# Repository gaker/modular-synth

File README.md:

# Modular Synth

A dumping ground for synthesizer modules, PCBs, etc.

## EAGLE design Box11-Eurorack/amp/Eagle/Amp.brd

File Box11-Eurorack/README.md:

# Box11 Eurorack

I love synthesizers.com modules. I also love eurorack modules This is an attempt to marry the two using a full-width faceplate to house 3U 
modules, as well as add in some other goodies.

I've gone with the [Box11 system](https://shop.synthesizers.com/products/qcb11) for all of my DotCom modules, and want to integrate those into eurorack. I've been rocking with the 64HP moog skiffs, they are full, so it is time to do something else.

The following gives me 104hp of eurorack space in a synthesizers.com Box 11 frame. With about 1.5U or so of space, I decided to go all in and have fun taking up the space.

## Faceplate

Status: in progress.

## Utilities

With ~1.5U of space just sitting there begging to have cables and modules
attached, I would be remiss if I didn't take advantage of all of this 
real estate.   

### 1/4" to 1/8" passive passthrough

* Switchcraft [35rm3s](https://www.switchcraft.com/3-5mm-stereo-jack-rear-mount-locking-sealed-rohs/35rm3s/) 1/8" Jacks
* Switchcraft [112ax](https://www.switchcraft.com/single-closed-circuit-solder-lug-termination/112ax/) 1/4" Jacks

### Fork

Simple 1 -> 3 (x2) buffered mults.

Power in:

    * +12V
    * -12V
    * GND

Via a [TE 640456-3](https://www.mouser.com/ProductDetail/571-6404563) from the Oscillator.

### Voice

VCO built on the [AS3340](https://www.alfarzpp.lv/eng/sc/AS3340.pdf) Oscillator.

### Sway

3x Attack/Release Envelope generators.
Gate one is normalized to gate 2

### Tone

VCF built on the [AS3320](https://www.alfarzpp.lv/eng/sc/AS3320.pdf)

### AMP

VCA built on the [AS3360](https://www.alfarzpp.lv/eng/sc/AS3360.pdf).
Powers two Hairball Audio 8045 VU Meters.

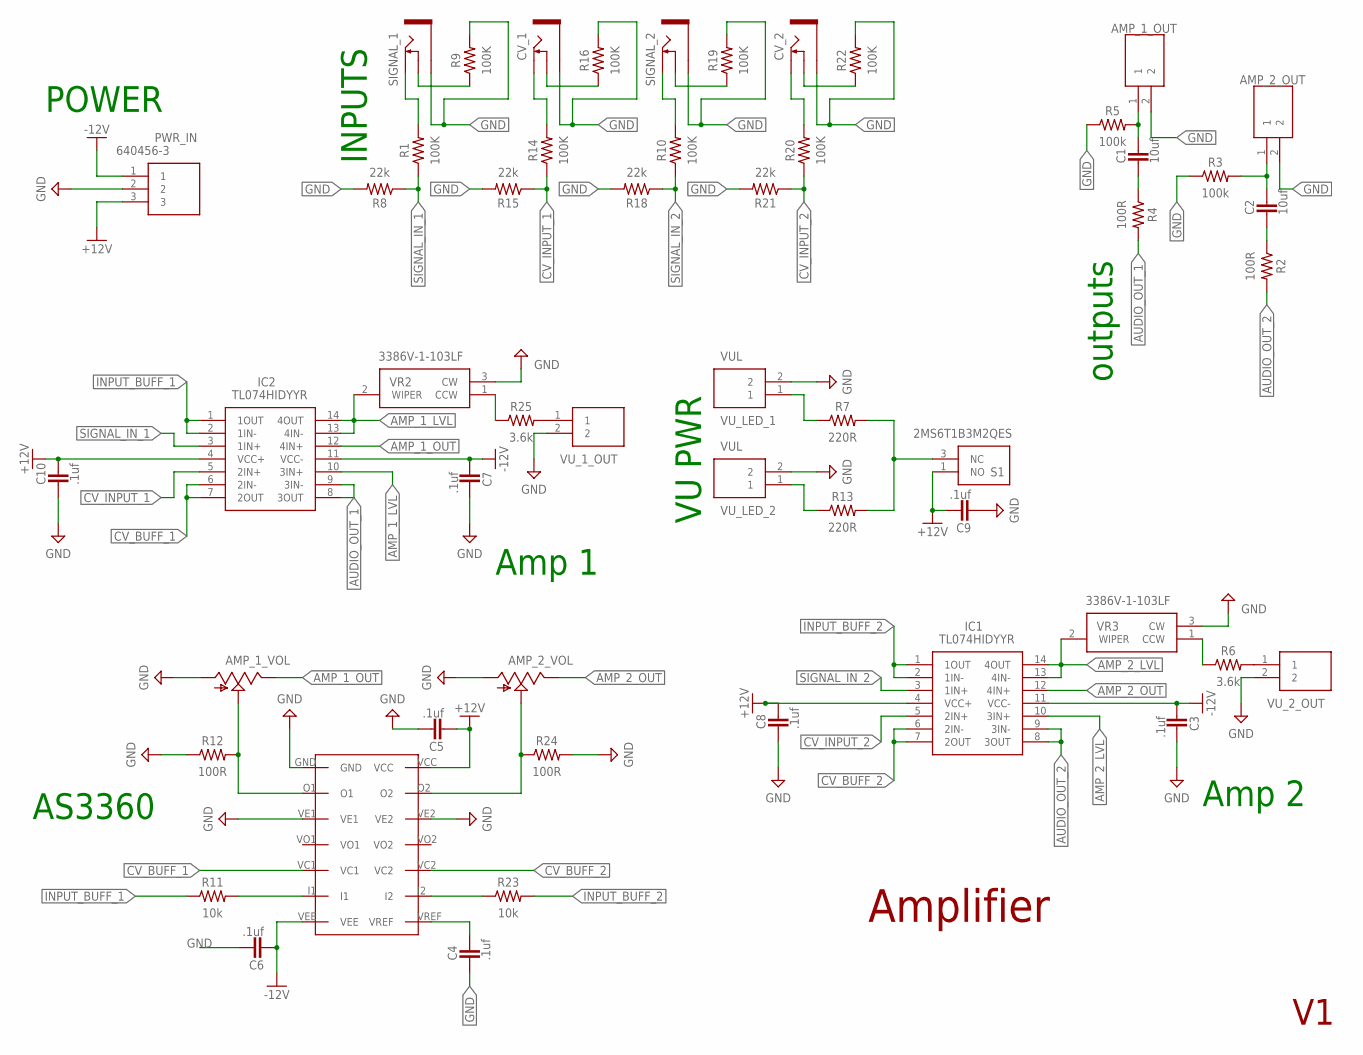
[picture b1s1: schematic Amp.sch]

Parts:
AMP_1_OUT, AMP_2_OUT: OUT; SHDR2W66P0X254_1X2_508X572X104
AMP_1_VOL, AMP_2_VOL: 9MM_SNAP-IN_POT_; 9MM_SNAP-IN_POT
C1, C2: 10uf; CAPM3216X180
C3, C4, C5, C6, C7, C8, C9, C10: .1uf; CAPC1005X60
CV_1, CV_2: THONKICONNNEW; WQP-PJ301M-12_JACK
IC1, IC2: TL074HIDYYR; SOP50P326X110-14N
PWR_IN: 640456-3; HDRV3W107P0X254_1X3_762X572X10
R1, R9, R10, R14, R16, R19, R20, R22: 100K; RESC1005X40
R2, R4, R12, R24: 100R; RESC1005X40
R3, R5: 100k; RESC1005X40
R6, R25: 3.6k; RESC1005X40
R7, R13: 220R; RESC1005X40
R8, R15, R18, R21: 22k; RESC1005X40
R11, R23: 10k; RESC1005X40
S1: 2MS6T1B3M2QES
SIGNAL_1, SIGNAL_2: THONKICONNNEW; WQP-PJ301M-12_JACK
U$1: AS3360
VR2, VR3: 3386V-1-103LF; 3386V1103LF
VU_1_OUT, VU_2_OUT: VUO; SHDR2W66P0X254_1X2_508X572X104
VU_LED_1, VU_LED_2: VUL; SHDR2W66P0X254_1X2_508X572X104

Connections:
+12V: C5.2, C8.1, C9.1, C10.1, IC1.4 (VCC+), IC2.4 (VCC+), PWR_IN.3, S1.1 (NO), U$1.VCC
-12V: C3.2, C6.2, C7.2, IC1.11 (VCC-), IC2.11 (VCC-), PWR_IN.1, U$1.VEE
AMP_1_LVL: IC2.10 (3IN+), IC2.13 (4IN-), IC2.14 (4OUT), VR2.2 (WIPER)
AMP_1_OUT: AMP_1_VOL.2 (S), AMP_1_VOL.3 (E), IC2.12 (4IN+), R12.2, U$1.O1
AMP_2_LVL: IC1.10 (3IN+), IC1.13 (4IN-), IC1.14 (4OUT), VR3.2 (WIPER)
AMP_2_OUT: AMP_2_VOL.2 (S), AMP_2_VOL.3 (E), IC1.12 (4IN+), R24.1, U$1.O2
AUDIO_OUT_1: IC2.8 (3OUT), IC2.9 (3IN-), R4.2
AUDIO_OUT_2: IC1.8 (3OUT), IC1.9 (3IN-), R2.2
CV_BUFF_1: IC2.6 (2IN-), IC2.7 (2OUT), U$1.VC1
CV_BUFF_2: IC1.6 (2IN-), IC1.7 (2OUT), U$1.VC2
CV_INPUT_1: IC2.5 (2IN+), R14.1, R15.1
CV_INPUT_2: IC1.5 (2IN+), R20.1, R21.1
GND: AMP_1_OUT.2, AMP_1_VOL.1 (A), AMP_2_OUT.2, AMP_2_VOL.1 (A), C3.1, C4.2, C5.1, C6.1, C7.1, C8.2, C9.2, C10.2, CV_1.P$3_SLEEVE (SLEEVE), CV_2.P$3_SLEEVE (SLEEVE), PWR_IN.2, R3.1, R5.1, R8.2, R9.2, R12.1, R15.2, R16.2, R18.2, R19.2, R21.2, R22.2, R24.2, SIGNAL_1.P$3_SLEEVE (SLEEVE), SIGNAL_2.P$3_SLEEVE (SLEEVE), U$1.GND, U$1.VE1, U$1.VE2, VR2.3 (CW), VR3.3 (CW), VU_1_OUT.2, VU_2_OUT.2, VU_LED_1.2, VU_LED_2.2
INPUT_BUFF_1: IC2.1 (1OUT), IC2.2 (1IN-), R11.1
INPUT_BUFF_2: IC1.1 (1OUT), IC1.2 (1IN-), R23.2
unnamed: AMP_2_OUT.1, C2.1, R3.2
unnamed: AMP_1_OUT.1, C1.1, R5.2
unnamed: C1.2, R4.1
unnamed: C2.2, R2.1
unnamed: R13.1, VU_LED_2.1
unnamed: R7.1, VU_LED_1.1
unnamed: C4.1, U$1.VREF
unnamed: R6.1, VR3.1 (CCW)
unnamed: R6.2, VU_2_OUT.1
unnamed: R11.2, U$1.I1
unnamed: R10.2, SIGNAL_2.P$1_TIP (TIP)
unnamed: R1.2, SIGNAL_1.P$1_TIP (TIP)
unnamed: R9.1, SIGNAL_1.P$2_SWITCH (SWITCH)
unnamed: CV_1.P$1_TIP (TIP), R14.2
unnamed: CV_1.P$2_SWITCH (SWITCH), R16.1
unnamed: R19.1, SIGNAL_2.P$2_SWITCH (SWITCH)
unnamed: CV_2.P$1_TIP (TIP), R20.2
unnamed: CV_2.P$2_SWITCH (SWITCH), R22.1
unnamed: R23.1, U$1.I2
unnamed: R7.2, R13.2, S1.3 (NC)
unnamed: R25.2, VU_1_OUT.1
unnamed: R25.1, VR2.1 (CCW)
SIGNAL_IN_1: IC2.3 (1IN+), R1.1, R8.1
SIGNAL_IN_2: IC1.3 (1IN+), R10.1, R18.1

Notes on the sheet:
Amplifier
POWER
outputs
AS3360
INPUTS
Amp 1
VU PWR
Amp 2

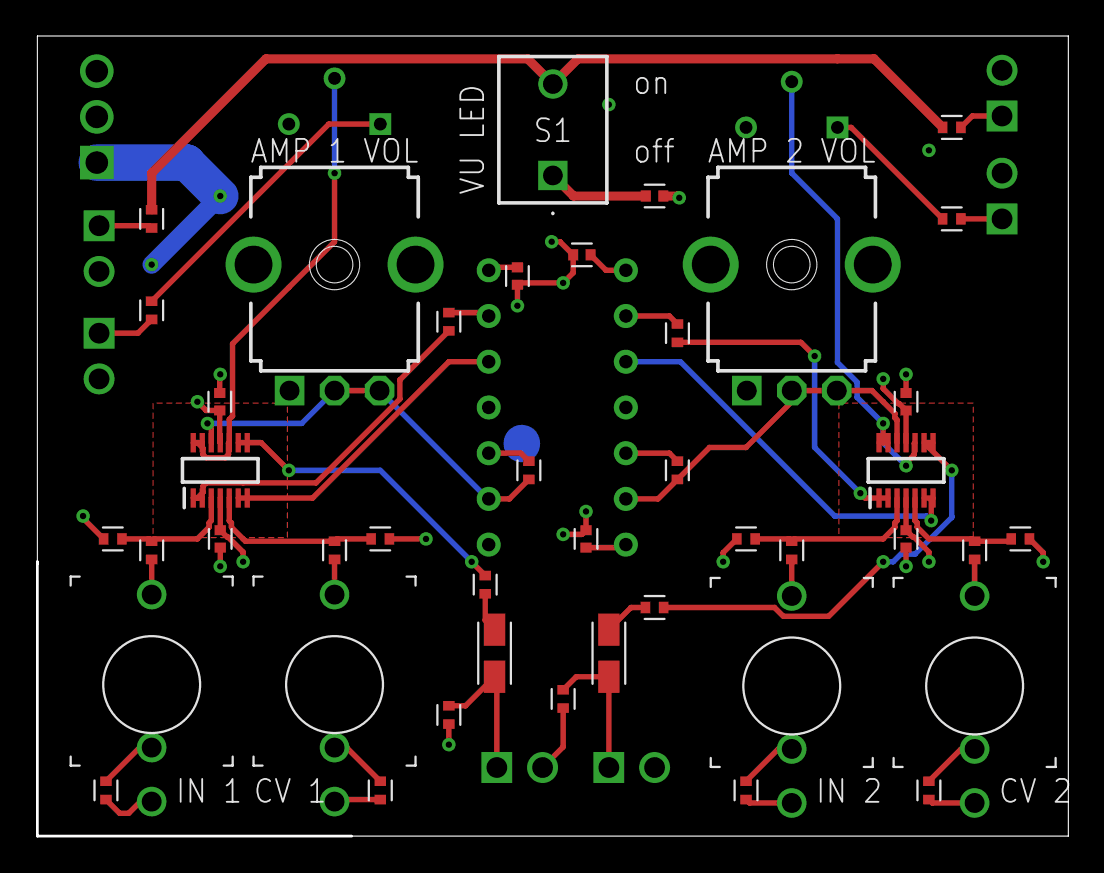
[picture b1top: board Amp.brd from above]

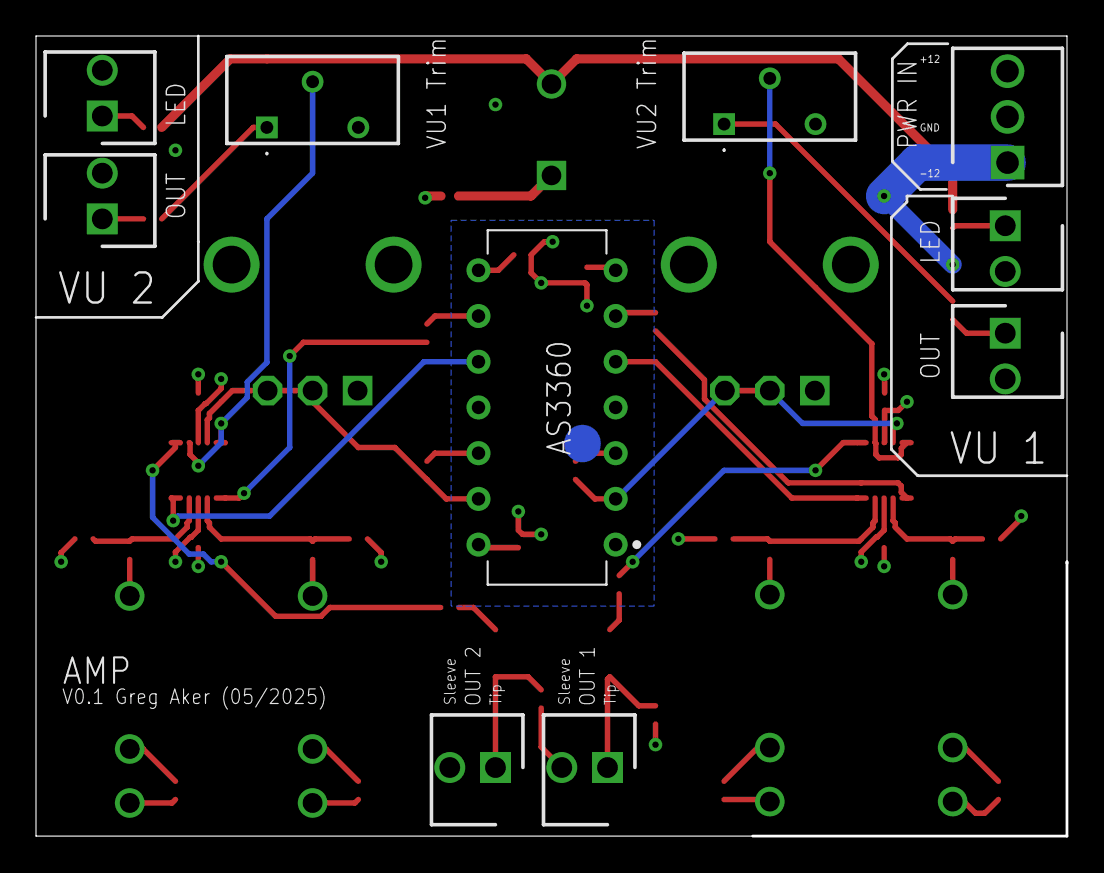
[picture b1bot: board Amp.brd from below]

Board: 4 copper layers, 57.2 x 44.4 mm, 53 parts (10 on the bottom side), 39 nets.

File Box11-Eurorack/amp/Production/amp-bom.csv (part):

Part,Value,Device,Package,Description,CATEGORY,DATASHEET,DESCRIPTION,HEIGHT,MANUFACTURER,MANUFACTURER_NAME,MANUFACTURER_PART_NUMBER,MOUSER_PART_NUMBER,MOUSER_PRICE-STOCK,MPN,OPERATING_TEMP,OPERATING_TEMPERATURE,PACKAGE_SIZE,PACKAGE_TYPE,PART_STATUS,ROHS,ROHS_COMPLIANT,SERIES,SPICEMODEL,SPICEMODELTEXT,SPICEPREFIX,SUB-CATEGORY,SUBCATEGORY,TEMPERATURE_COEFFICIENT,THERMALLOSS,TOLERANCE,TYPE,VOLTAGE_RATING
AMP_1_OUT,OUT,640456-2,SHDR2W66P0X254_1X2_508X572X104,"Body Features: Primary Product Color Natural | Configuration Features: Number of Positions 2 | Number of Columns 2 | PCB Mount Orientation Vertical | Number of Rows 1 | Contact Features: Contact Mating Area Length 7.49 MM | Contact Shape & Form Square | Contact Layout Inline | Contact Mating Area Plating Material Thickness 3.81 MICM | Contact Mating Area Plating Material Thickness 150 MICIN | Contact Underplating Material Thickness 1.27 MICM | Contact Mating Area Length .295 INCH | PCB Contact Termination A",,,"Body Features: Primary Product Color Natural | Configuration Features: Number of Positions 2 | Number of Columns 2 | PCB Mount Orientation Vertical | Number of Rows 1 | Contact Features: Contact Mating Area Length 7.49 MM | Contact Shape & Form Square | Contact Layout Inline | Contact Mating Area Plating Material Thickness 3.81 MICM | Contact Mating Area Plating Material Thickness 150 MICIN | Contact Underplating Material Thickness 1.27 MICM | Contact Mating Area Length .295 INCH | PCB Contact Termination A",10.414mm,,"TE Connectivity",640456-2,571-6404562,https://www.mouser.co.uk/ProductDetail/TE-Connectivity-AMP/6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,,,,,,,,,,OutputJack,"*\n.subckt OutputJack 1 2\nR1 1 1_dummy 1m\nR2 2 2_dummy 1m\n.ends OutputJack",X,,,,,,,
AMP_1_VOL,,9MM_SNAP-IN_POT_,9MM_SNAP-IN_POT,"9mm vertical snap-in pot, Alpha / Panasonic style",,,,,,,,,,,,,,,,,,,POT10K,"*\n.subckt POT10K 1 2 3\nRtop 1 2 5k\nRbot 2 3 5k\n.ends POT10K",X,,,,,,,
AMP_2_OUT,OUT,640456-2,SHDR2W66P0X254_1X2_508X572X104,"Body Features: Primary Product Color Natural | Configuration Features: Number of Positions 2 | Number of Columns 2 | PCB Mount Orientation Vertical | Number of Rows 1 | Contact Features: Contact Mating Area Length 7.49 MM | Contact Shape & Form Square | Contact Layout Inline | Contact Mating Area Plating Material Thickness 3.81 MICM | Contact Mating Area Plating Material Thickness 150 MICIN | Contact Underplating Material Thickness 1.27 MICM | Contact Mating Area Length .295 INCH | PCB Contact Termination A",,,"Body Features: Primary Product Color Natural | Configuration Features: Number of Positions 2 | Number of Columns 2 | PCB Mount Orientation Vertical | Number of Rows 1 | Contact Features: Contact Mating Area Length 7.49 MM | Contact Shape & Form Square | Contact Layout Inline | Contact Mating Area Plating Material Thickness 3.81 MICM | Contact Mating Area Plating Material Thickness 150 MICIN | Contact Underplating Material Thickness 1.27 MICM | Contact Mating Area Length .295 INCH | PCB Contact Termination A",10.414mm,,"TE Connectivity",640456-2,571-6404562,https://www.mouser.co.uk/ProductDetail/TE-Connectivity-AMP/6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,,,,,,,,,,OutputJack,"*\n.subckt OutputJack 1 2\nR1 1 1_dummy 1m\nR2 2 2_dummy 1m\n.ends OutputJack",X,,,,,,,
AMP_2_VOL,,9MM_SNAP-IN_POT_,9MM_SNAP-IN_POT,"9mm vertical snap-in pot, Alpha / Panasonic style",,,,,,,,,,,,,,,,,,,POT10K,"*\n.subckt POT10K 1 2 3\nRtop 1 2 5k\nRbot 2 3 5k\n.ends POT10K",X,,,,,,,
C1,10uf,CAPACITOR_TANTALUM-1206(3216-METRIC),CAPM3216X180,"Capacitor - Generic",Capacitor,,,,,,,,,,,,,,,,,,,,,,,,,,,
C2,10uf,CAPACITOR_TANTALUM-1206(3216-METRIC),CAPM3216X180,"Capacitor - Generic",Capacitor,,,,,,,,,,,,,,,,,,,,,,,,,,,
C3,.1uf,CAPACITOR_CHIP-0402(1005-METRIC),CAPC1005X60,"Capacitor - Generic",Capacitor,,,,,,,,,,,,,,,,,,,,,,,,,,,
C4,.1uf,CAPACITOR_CHIP-0402(1005-METRIC),CAPC1005X60,"Capacitor - Generic",Capacitor,,,,,,,,,,,,,,,,,,,,,,,,,,,
C5,.1uf,CAPACITOR_CHIP-0402(1005-METRIC),CAPC1005X60,"Capacitor - Generic",Capacitor,,,,,,,,,,,,,,,,,,,,,,,,,,,
C6,.1uf,CAPACITOR_CHIP-0402(1005-METRIC),CAPC1005X60,"Capacitor - Generic",Capacitor,,,,,,,,,,,,,,,,,,,,,,,,,,,
C7,.1uf,CAPACITOR_CHIP-0402(1005-METRIC),CAPC1005X60,"Capacitor - Generic",Capacitor,,,,,,,,,,,,,,,,,,,,,,,,,,,
C8,.1uf,CAPACITOR_CHIP-0402(1005-METRIC),CAPC1005X60,"Capacitor - Generic",Capacitor,,,,,,,,,,,,,,,,,,,,,,,,,,,
C9,.1uf,CAPACITOR_CHIP-0402(1005-METRIC),CAPC1005X60,"Capacitor - Generic",Capacitor,,,,,,,,,,,,,,,,,,,,,,,,,,,
C10,.1uf,CAPACITOR_CHIP-0402(1005-METRIC),CAPC1005X60,"Capacitor - Generic",Capacitor,,,,,,,,,,,,,,,,,,,,,,,,,,,
CV_1,THONKICONNNEW,THONKICONNNEW,WQP-PJ301M-12_JACK,"3.5mm socket for Eurorack modular synths",,,,,,,,,,,,,,,,,,,,,,,,,,,,
CV_2,THONKICONNNEW,THONKICONNNEW,WQP-PJ301M-12_JACK,"3.5mm socket for Eurorack modular synths",,,,,,,,,,,,,,,,,,,,,,,,,,,,
IC1,TL074HIDYYR,TL074HIDYYR,SOP50P326X110-14N,"Operational Amplifiers - Op Amps Quad, 40-V, 5-MHz, 4-mV offset voltage, 20-V/us, In to V+ op amp with -40 C to 125 C operation",,,"Operational Amplifiers - Op Amps Quad"," 40-V"," 5-MHz"," 4-mV offset voltage"," 20-V/us"," In to V+ op amp with -40 C to 125 C operation",1.1mm,,"Texas Instruments",TL074HIDYYR,595-TL074HIDYYR,https://www.mouser.co.uk/ProductDetail/Texas-Instruments/TL0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,,,,,,,,,,,,,,
IC2,TL074HIDYYR,TL074HIDYYR,SOP50P326X110-14N,"Operational Amplifiers - Op Amps Quad, 40-V, 5-MHz, 4-mV offset voltage, 20-V/us, In to V+ op amp with -40 C to 125 C operation",,,"Operational Amplifiers - Op Amps Quad"," 40-V"," 5-MHz"," 4-mV offset voltage"," 20-V/us"," In to V+ op amp with -40 C to 125 C operation",1.1mm,,"Texas Instruments",TL074HIDYYR,595-TL074HIDYYR,https://www.mouser.co.uk/ProductDetail/Texas-Instruments/TL0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,,,,,,,,,,,,,,
PWR_IN,640456-3,640456-3,HDRV3W107P0X254_1X3_762X572X10,"Body Features: Primary Product Color Natural | Configuration Features: Number of Positions 3 | PCB Mount Orientation Vertical | Number of Rows 1 | Contact Features: Contact Current Rating (Max) 5 AMP | Contact Mating Area Plating Material Tin | Contact Underplating Material Nickel | PCB Contact Termination Area Plating Material Tin | Contact Mating Area Length 7.49 MM | Contact Underplating Material Thickness 50 MICIN | Contact Layout Inline | Contact Mating Area Length .295 INCH | Contact Base Material Cop",,,"Body Features: Primary Product Color Natural | Configuration Features: Number of Positions 3 | PCB Mount Orientation Vertical | Number of Rows 1 | Contact Features: Contact Current Rating (Max) 5 AMP | Contact Mating Area Plating Material Tin | Contact Underplating Material Nickel | PCB Contact Termination Area Plating Material Tin | Contact Mating Area Length 7.49 MM | Contact Underplating Material Thickness 50 MICIN | Contact Layout Inline | Contact Mating Area Length .295 INCH | Contact Base Material Cop",10.795mm,,"TE Connectivity",640456-3,571-6404563,https://www.mouser.co.uk/ProductDetail/TE-Connectivity-AMP/6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,,,,,,,,,,,,,,,,,,,
R1,100K,R-US_CHIP-0402(1005-METRIC),RESC1005X40,"Resistor Fixed - ANSI",Resistors,,"Chip Resistor 1.05 X 0.54 X 0.40 mm body 0402(1005-METRIC) Package",,,,,,,,,,0402,SMD,,,,,,,,,,,,,,
R2,100R,R-US_CHIP-0402(1005-METRIC),RESC1005X40,"Resistor Fixed - ANSI",Resistors,,"Chip Resistor 1.05 X 0.54 X 0.40 mm body 0402(1005-METRIC) Package",,,,,,,,,,0402,SMD,,,,,,,,,,,,,,
R3,100k,R-US_CHIP-0402(1005-METRIC),RESC1005X40,"Resistor Fixed - ANSI",Resistors,,"Chip Resistor 1.05 X 0.54 X 0.40 mm body 0402(1005-METRIC) Package",,,,,,,,,,0402,SMD,,,,,,,,,,,,,,
R4,100R,R-US_CHIP-0402(1005-METRIC),RESC1005X40,"Resistor Fixed - ANSI",Resistors,,"Chip Resistor 1.05 X 0.54 X 0.40 mm body 0402(1005-METRIC) Package",,,,,,,,,,0402,SMD,,,,,,,,,,,,,,
R5,100k,R-US_CHIP-0402(1005-METRIC),RESC1005X40,"Resistor Fixed - ANSI",Resistors,,"Chip Resistor 1.05 X 0.54 X 0.40 mm body 0402(1005-METRIC) Package",,,,,,,,,,0402,SMD,,,,,,,,,,,,,,
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
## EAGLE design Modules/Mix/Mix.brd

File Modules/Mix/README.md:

# Mixer

Here's a very simple mixer 

| Part | Quantity |
|----------|----------|
| [Thonkiconn](https://www.thonk.co.uk/shop/thonkiconn/) | 6 |
| [100k Log Potentiometer](https://www.taydaelectronics.com/100k-ohm-logarithmic-taper-potentiometer-round-shaft-pcb-9mm.html) | 3 |

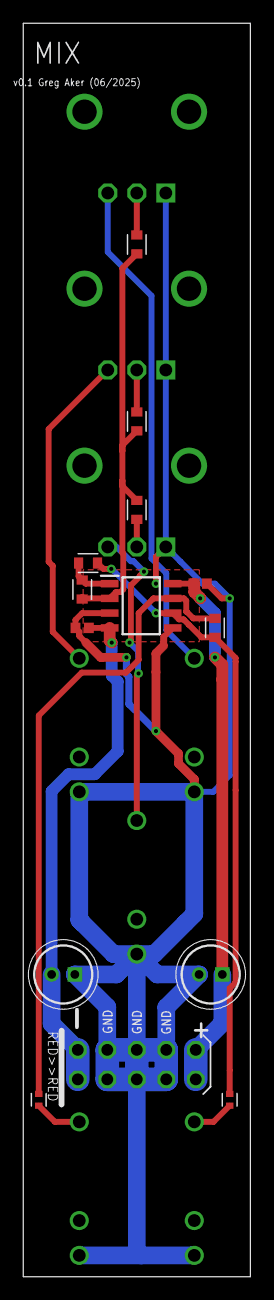
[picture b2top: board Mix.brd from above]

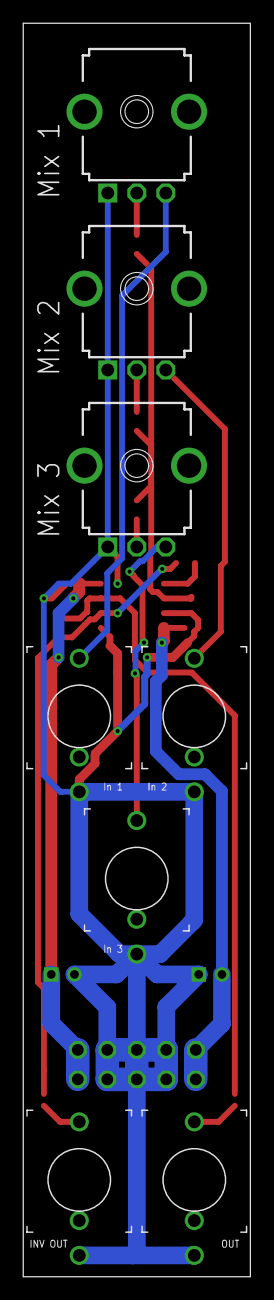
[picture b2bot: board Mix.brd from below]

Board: 2 copper layers, 19.6 x 108.0 mm, 22 parts (8 on the bottom side), 15 nets.

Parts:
C1, C2: 10uf; CAPPRD200W55D500H1200
C3, C4: 0.1uF; 0402
IC1: TL072BIDT; SOIC127P600X175-8N
INV_OUT: THONKICONNNEW; WQP-PJ301M-12_JACK
IN_1, IN_2, IN_3: THONKICONNNEW; WQP-PJ301M-12_JACK
OUT: THONKICONNNEW; WQP-PJ301M-12_JACK
R1, R2, R3, R4, R5, R6: 120k; RESC1608X60
R7, R8: 1k; RESC1005X40
SV1: EURO_POWER_HEADERREGULAR; EURO_POWER_HEADER
VR1, VR2, VR3: 50k; 9MM_SNAP-IN_POT

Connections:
+12V: C2.1, C4.1, IC1.8, SV1.9, SV1.10
-12V: C1.2, C3.1, IC1.4, SV1.1, SV1.2
GND: C1.1, C2.2, C3.2, C4.2, IC1.3, IC1.5, INV_OUT.P$3_SLEEVE, IN_1.P$3_SLEEVE, IN_2.P$3_SLEEVE, IN_3.P$3_SLEEVE, OUT.P$3_SLEEVE, SV1.3, SV1.4, SV1.5, SV1.6, SV1.7, SV1.8, VR1.1, VR2.1, VR3.1
unnamed: IN_1.P$1_TIP, VR1.3
unnamed: IN_2.P$1_TIP, VR2.3
unnamed: IN_3.P$1_TIP, VR3.3
unnamed: R1.1, VR1.2
unnamed: R2.1, VR2.2
unnamed: R3.1, VR3.2
unnamed: IC1.1, R4.2, R5.1
unnamed: IC1.6, R5.2, R6.1, R7.1
unnamed: IC1.2, R1.2, R2.2, R3.2, R4.1
unnamed: IC1.7, R6.2, R8.1
unnamed: INV_OUT.P$1_TIP, R7.2
unnamed: OUT.P$1_TIP, R8.2

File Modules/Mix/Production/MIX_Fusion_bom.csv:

Part,Value,Device,Package,Description,CATEGORY,DATASHEET,DESCRIPTION,HEIGHT,MANUFACTURER,MANUFACTURER_NAME,MANUFACTURER_PART_NUMBER,MOUSER_PART_NUMBER,MOUSER_PRICE-STOCK,MPN,OPERATING_TEMPERATURE,PACKAGE_SIZE,PACKAGE_TYPE,PART_STATUS,PROD_ID,ROHS,SERIES,SUBCATEGORY,TEMPERATURE_COEFFICIENT,THERMALLOSS,TOLERANCE,TYPE,VALUE
C1,10uf,ECE-A1EN100U,CAPPRD200W55D500H1200,"Panasonic 10uF 25 V Aluminium Electrolytic Capacitor, SU Series 1000h 5 x 11mm",,,"Panasonic 10uF 25 V Aluminium Electrolytic Capacitor"," SU Series 1000h 5 x 11mm",12mm,,Panasonic,ECE-A1EN100U,667-ECE-A1EN100U,https://www.mouser.co.uk/ProductDetail/Panasonic/ECE-A1EN100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,,,,,,,,,,,,,
C2,10uf,ECE-A1EN100U,CAPPRD200W55D500H1200,"Panasonic 10uF 25 V Aluminium Electrolytic Capacitor, SU Series 1000h 5 x 11mm",,,"Panasonic 10uF 25 V Aluminium Electrolytic Capacitor"," SU Series 1000h 5 x 11mm",12mm,,Panasonic,ECE-A1EN100U,667-ECE-A1EN100U,https://www.mouser.co.uk/ProductDetail/Panasonic/ECE-A1EN100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,,,,,,,,,,,,,
C3,0.1uF,0.1UF-0402-16V-10%,0402,"0.1µF ceramic capacitors",,,,,,,,,,,,,,,CAP-12416,,,,,,,,0.1uF
C4,0.1uF,0.1UF-0402-16V-10%,0402,"0.1µF ceramic capacitors",,,,,,,,,,,,,,,CAP-12416,,,,,,,,0.1uF
IC1,TL072BIDT,TL072BIDT,SOIC127P600X175-8N,"STMICROELECTRONICS - TL072BIDT - Operational Amplifier, 2 Amplifier, 4 MHz, 16 V/s, 6V to 36V, SOIC, 8 Pins",,,"STMICROELECTRONICS - TL072BIDT - Operational Amplifier"," 2 Amplifier"," 4 MHz"," 16 V/s"," 6V to 36V"," SOIC"," 8 Pins",1.75mm,,STMicroelectronics,TL072BIDT,511-TL072BIDT,https://www.mouser.co.uk/ProductDetail/STMicroelectronics/TL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,,,,,,,,
INV_OUT,THONKICONNNEW,THONKICONNNEW,WQP-PJ301M-12_JACK,"3.5mm socket for Eurorack modular synths",,,,,,,,,,,,,,,,,,,,,,,
IN_1,THONKICONNNEW,THONKICONNNEW,WQP-PJ301M-12_JACK,"3.5mm socket for Eurorack modular synths",,,,,,,,,,,,,,,,,,,,,,,
IN_2,THONKICONNNEW,THONKICONNNEW,WQP-PJ301M-12_JACK,"3.5mm socket for Eurorack modular synths",,,,,,,,,,,,,,,,,,,,,,,
IN_3,THONKICONNNEW,THONKICONNNEW,WQP-PJ301M-12_JACK,"3.5mm socket for Eurorack modular synths",,,,,,,,,,,,,,,,,,,,,,,
OUT,THONKICONNNEW,THONKICONNNEW,WQP-PJ301M-12_JACK,"3.5mm socket for Eurorack modular synths",,,,,,,,,,,,,,,,,,,,,,,
R1,120k,R_CHIP-0603(1608-METRIC),RESC1608X60,"Resistor Fixed - Generic",Resistors,,"Chip Resistor 1.60 X 0.82 X 0.60 mm body 0603(1608-METRIC) Package",,,,,,,,,0603,SMD,,,,,,,,,,
R2,120k,R_CHIP-0603(1608-METRIC),RESC1608X60,"Resistor Fixed - Generic",Resistors,,"Chip Resistor 1.60 X 0.82 X 0.60 mm body 0603(1608-METRIC) Package",,,,,,,,,0603,SMD,,,,,,,,,,
R3,120k,R_CHIP-0603(1608-METRIC),RESC1608X60,"Resistor Fixed - Generic",Resistors,,"Chip Resistor 1.60 X 0.82 X 0.60 mm body 0603(1608-METRIC) Package",,,,,,,,,0603,SMD,,,,,,,,,,
R4,120k,R_CHIP-0603(1608-METRIC),RESC1608X60,"Resistor Fixed - Generic",Resistors,,"Chip Resistor 1.60 X 0.82 X 0.60 mm body 0603(1608-METRIC) Package",,,,,,,,,0603,SMD,,,,,,,,,,
R5,120k,R_CHIP-0603(1608-METRIC),RESC1608X60,"Resistor Fixed - Generic",Resistors,,"Chip Resistor 1.60 X 0.82 X 0.60 mm body 0603(1608-METRIC) Package",,,,,,,,,0603,SMD,,,,,,,,,,
R6,120k,R_CHIP-0603(1608-METRIC),RESC1608X60,"Resistor Fixed - Generic",Resistors,,"Chip Resistor 1.60 X 0.82 X 0.60 mm body 0603(1608-METRIC) Package",,,,,,,,,0603,SMD,,,,,,,,,,
R7,1k,R_CHIP-0402(1005-METRIC),RESC1005X40,"Resistor Fixed - Generic",Resistors,,"Chip Resistor 1.05 X 0.54 X 0.40 mm body 0402(1005-METRIC) Package",,,,,,,,,0402,SMD,,,,,,,,,,
R8,1k,R_CHIP-0402(1005-METRIC),RESC1005X40,"Resistor Fixed - Generic",Resistors,,"Chip Resistor 1.05 X 0.54 X 0.40 mm body 0402(1005-METRIC) Package",,,,,,,,,0402,SMD,,,,,,,,,,
SV1,EURO_POWER_HEADERREGULAR,EURO_POWER_HEADERREGULAR,EURO_POWER_HEADER,"Power Header",,,,,,,,,,,,,,,,,,,,,,,
VR1,50k,9MM_SNAP-IN_POT_,9MM_SNAP-IN_POT,"9mm vertical snap-in pot, Alpha / Panasonic style",,,,,,,,,,,,,,,,,,,,,,,
VR2,50k,9MM_SNAP-IN_POT_,9MM_SNAP-IN_POT,"9mm vertical snap-in pot, Alpha / Panasonic style",,,,,,,,,,,,,,,,,,,,,,,
VR3,50k,9MM_SNAP-IN_POT_,9MM_SNAP-IN_POT,"9mm vertical snap-in pot, Alpha / Panasonic style",,,,,,,,,,,,,,,,,,,,,,,

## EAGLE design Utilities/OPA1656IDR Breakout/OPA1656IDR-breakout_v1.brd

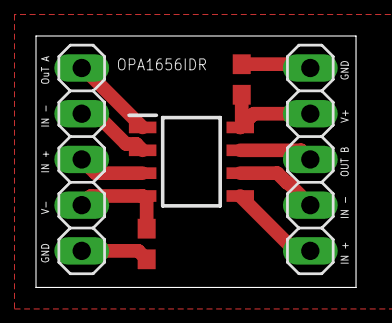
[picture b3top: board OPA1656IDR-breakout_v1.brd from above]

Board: 2 copper layers, 17.8 x 14.0 mm, 5 parts (0 on the bottom side), 9 nets.

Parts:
C1, C2: 0.1uF; 0603
IC1: OPA1656IDR; SOIC127P600X175-8N
JP1, JP2: PINHD-1X5; 1X05

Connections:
GND: C1.1, C2.2, JP1.5, JP2.1
unnamed: IC1.1, JP1.1
unnamed: IC1.2, JP1.2
unnamed: IC1.3, JP1.3
unnamed: C2.1, IC1.4, JP1.4
unnamed: IC1.5, JP2.5
unnamed: IC1.6, JP2.4
unnamed: IC1.7, JP2.3
unnamed: C1.2, IC1.8, JP2.2

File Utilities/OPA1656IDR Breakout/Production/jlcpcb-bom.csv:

Comment,Designator,Footprint,JLCPCB Part #（optional）
0.1uF,C1,0603,C14663
0.1uF,C2,0603,C14663
OPA1656IDR,IC1,SOIC127P600X175-8N,C1849431
,,,
,,,
,,,
,,,

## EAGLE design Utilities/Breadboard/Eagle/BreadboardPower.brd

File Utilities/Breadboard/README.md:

# Breadboard

Simple breadboard adapter for a Meanwell RT65B.

* Provides power filtering to save space on the breadboard.
* +12V/GND / -12V/GND rails to fit on either side of the breadboard.
* Pin header for +3.3v & 5V

Uses a ``TE-Connectivity-AMP/640456-6`` connector to supply power to the board.  Sorry in advance. I have a crimper that can make these cables. If anyone wants a board with something different, I can make one if you wish.

| Pin | Usage |
|-----|-------|
| 1   | +5V   |
| 2   | GND   |
| 3   | NC    |
| 4   | +12V  |
| 5   | NC    |
| 6   | -12V  |

## Cost

Manufactured at [JLCPCB](https://www.jlcpcb.com) in July of 2025 with PCBA assembly (see Production directory for more info).

*PCBA for 5 boards*

| Item                    | Cost       |
|-------------------------|------------|
| Merchandise Total       | $15.75     |
| Shipping Charge         | $37.39     |
| Customs duties & taxes  | $8.67      |
| Sales Tax               | $4.25      |
| **Order Total**         | **$66.06** | 

## Safety with the power supply

Your mileage may vary, and do this at your own risk, k?  This power supply is a bit scary for desk usage since the line-level voltages can easily be touched. That could mean a very bad day for you and your loved ones.  I wired up a line cord and then used hot glue to cover the terminals taking extra care to test continuity everywhere to ensure this doesn't shock me by being on my benchtop.  I also keep it in a little box I drilled holes into. 

But you do you. Whatever you think makes sense.

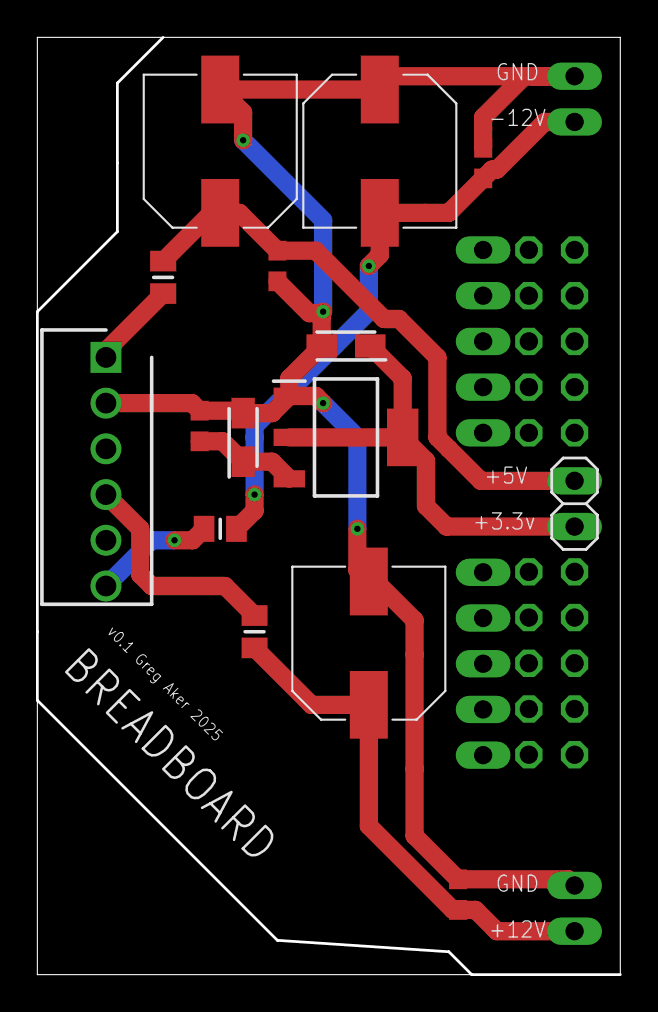
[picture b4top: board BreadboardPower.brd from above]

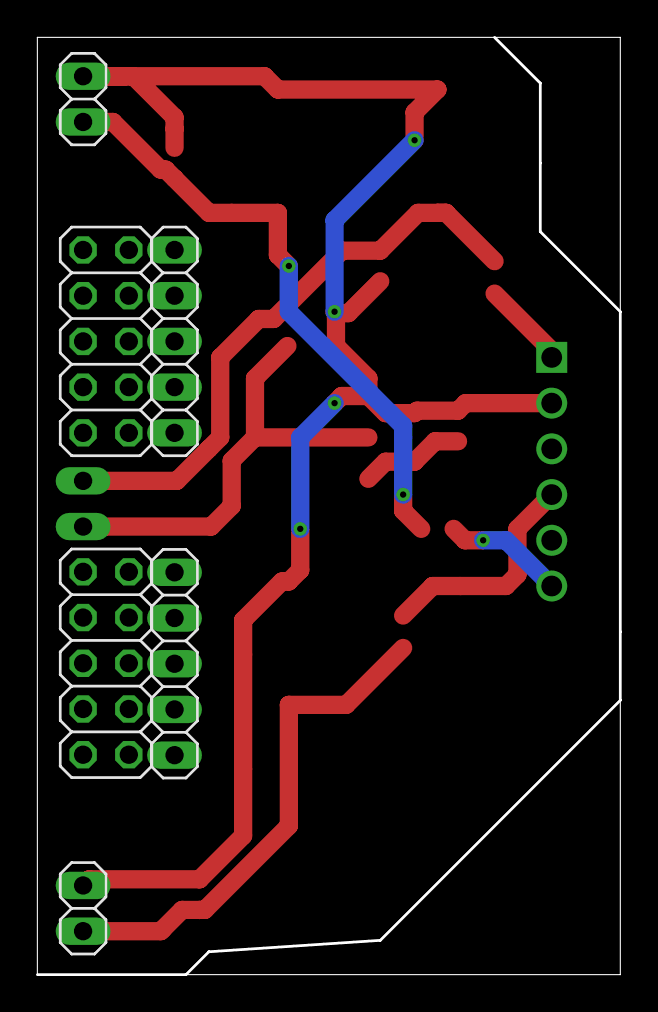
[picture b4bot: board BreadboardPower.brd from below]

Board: 2 copper layers, 32.4 x 52.1 mm, 21 parts (6 on the bottom side), 9 nets.

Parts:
C1, C2, C6: 220uf; CAPAE830X1050N
C3, C4, C5, C11: 0.1uF; 0603
C9, C10: TAJA106K016RNJ; CAPPM3216X180N
FB1, FB2, FB3: BLM21PG300SN1D; BEADC2012X105N
IC2: LM1117MPX-3.3_NOPB; SOT230P700X180-4N
J1: 640456-6; SHDR6W66P0X254_1X6_1524X572X10
JP1, JP2, JP5: PINHD-1X2; 1X02
JP3, JP4: PINHD-1X5; 1X05
JP6, JP7: PINHD-2X5; 2X05

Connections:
3.3V: C9.1, IC2.2, IC2.4, JP5.2
5V_FILTERED: C10.1, C11.1, IC2.3
+5V_FILTERED: C5.2, C6.1, FB3.2, JP5.1
+5_RAW: FB3.1, J1.1
+12V: C2.1, C4.2, FB2.2, JP2.1
-12V: C1.2, C3.2, FB1.2, JP1.1
-12VIN: FB1.1, J1.6
GND: C1.1, C2.2, C3.1, C4.1, C5.1, C6.2, C9.2, C10.2, C11.2, IC2.1, J1.2, JP1.2, JP2.2
unnamed: FB2.1, J1.4

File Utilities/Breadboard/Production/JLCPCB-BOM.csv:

Comment,Designator,Footprint,JLCPCB Part #（optional）
220uf,"C1,C2,C6","SMD,D8xL10.5mm",C97814
0.1uf,"C3,C4,C5,C11",0603,C14663
14mΩ ±25% 30Ω@100MHz 0805 Ferrite Beads ROHS,"FB1,FB2,FB3",0805,C16903
"1A 60dB@(120Hz) Fixed 3.3V Positive electrode 12V SOT-223 Voltage Regulators - Linear, Low Drop Out (LDO) Regulators ROHS",IC2,SOT-223,C347222
10uF 16V 3Ω@100kHz ±10% CASE-A-3216-18(mm) Tantalum Capacitors ROHS,"C9,C10",CASE-A-3216-18(mm),C7171
,,,
,,,

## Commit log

2025-07-06 Breadboarding power supply connector
2025-07-06 A simple mixer module
2025-07-06 Power
2025-07-06 OPA1612/OPA1656 breakout boards
2025-07-06 Mix updates

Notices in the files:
parts and their libraries:
SparkFun-Capacitors: Licensing: Creative Commons ShareAlike 4.0 International - https://creativecommons.org/licenses/by-sa/4.0
